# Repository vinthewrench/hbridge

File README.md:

# Actuator Controller – I²C Smart H-Bridge Board

This board is a smart linear actuator controller that uses a VNH7100BAS H-bridge with current sensing and I²C control. It is designed for 12 V actuators, supports stall/jam detection, and is chainable over I²C so you can run multiple actuators from one controller without burning GPIO pins.

This board is part of my distributed control system and is compatible with my nodeLync I²C wiring standard.

## Features
- Drives 12 V linear actuators (extend/retract)
- Solid-state H-bridge (no relays to weld shut)
- Current sensing for stall/jam detection
- I²C control using MCP23008 GPIO expander
- Optional MCP3427 ADC for current telemetry
- Motor power terminal or Anderson Powerpole input
- Status LEDs for power and activity
- Designed for Raspberry Pi or microcontroller systems
- Open hardware – modify it, build it, use it

## I²C Addresses
	| Device        | Base Address | Configurable         |
	|---------------|--------------|----------------------|
	| MCP23008 GPIO | 0x20–0x27    | Yes (A0–A2 jumpers)  |
	| MCP3427 ADC   | 0x68–0x6B    | Yes (ADDR pin)       |

## Current Measurement
The VNH7100BAS provides a current sense output. In 12-bit mode:
Useful for overload protection and detecting mechanical faults.

## Documentation
Full design writeup:
https://www.vinthewrench.com/p/the-humble-actuator

Demo video:
https://youtu.be/HOyxq8rQfaQ

## Status
✅ Prototype tested  
✅ Verified on Raspberry Pi  
✅ Load tested with Progressive Automations PA-10 and PA-14 actuators  
✅ Ready for fabrication / community mods

## License
This is Open Hardware under the CERN-OHL-P v2 license.

You can build it, modify it, use it commercially, and keep modifications private if you want. Just do not remove the original credit.

SPDX-License-Identifier: CERN-OHL-P-2.0  
© 2025 Vinnie Moscaritolo

## Contributions
Issues and pull requests are welcome. If you build one, I would like to see it.

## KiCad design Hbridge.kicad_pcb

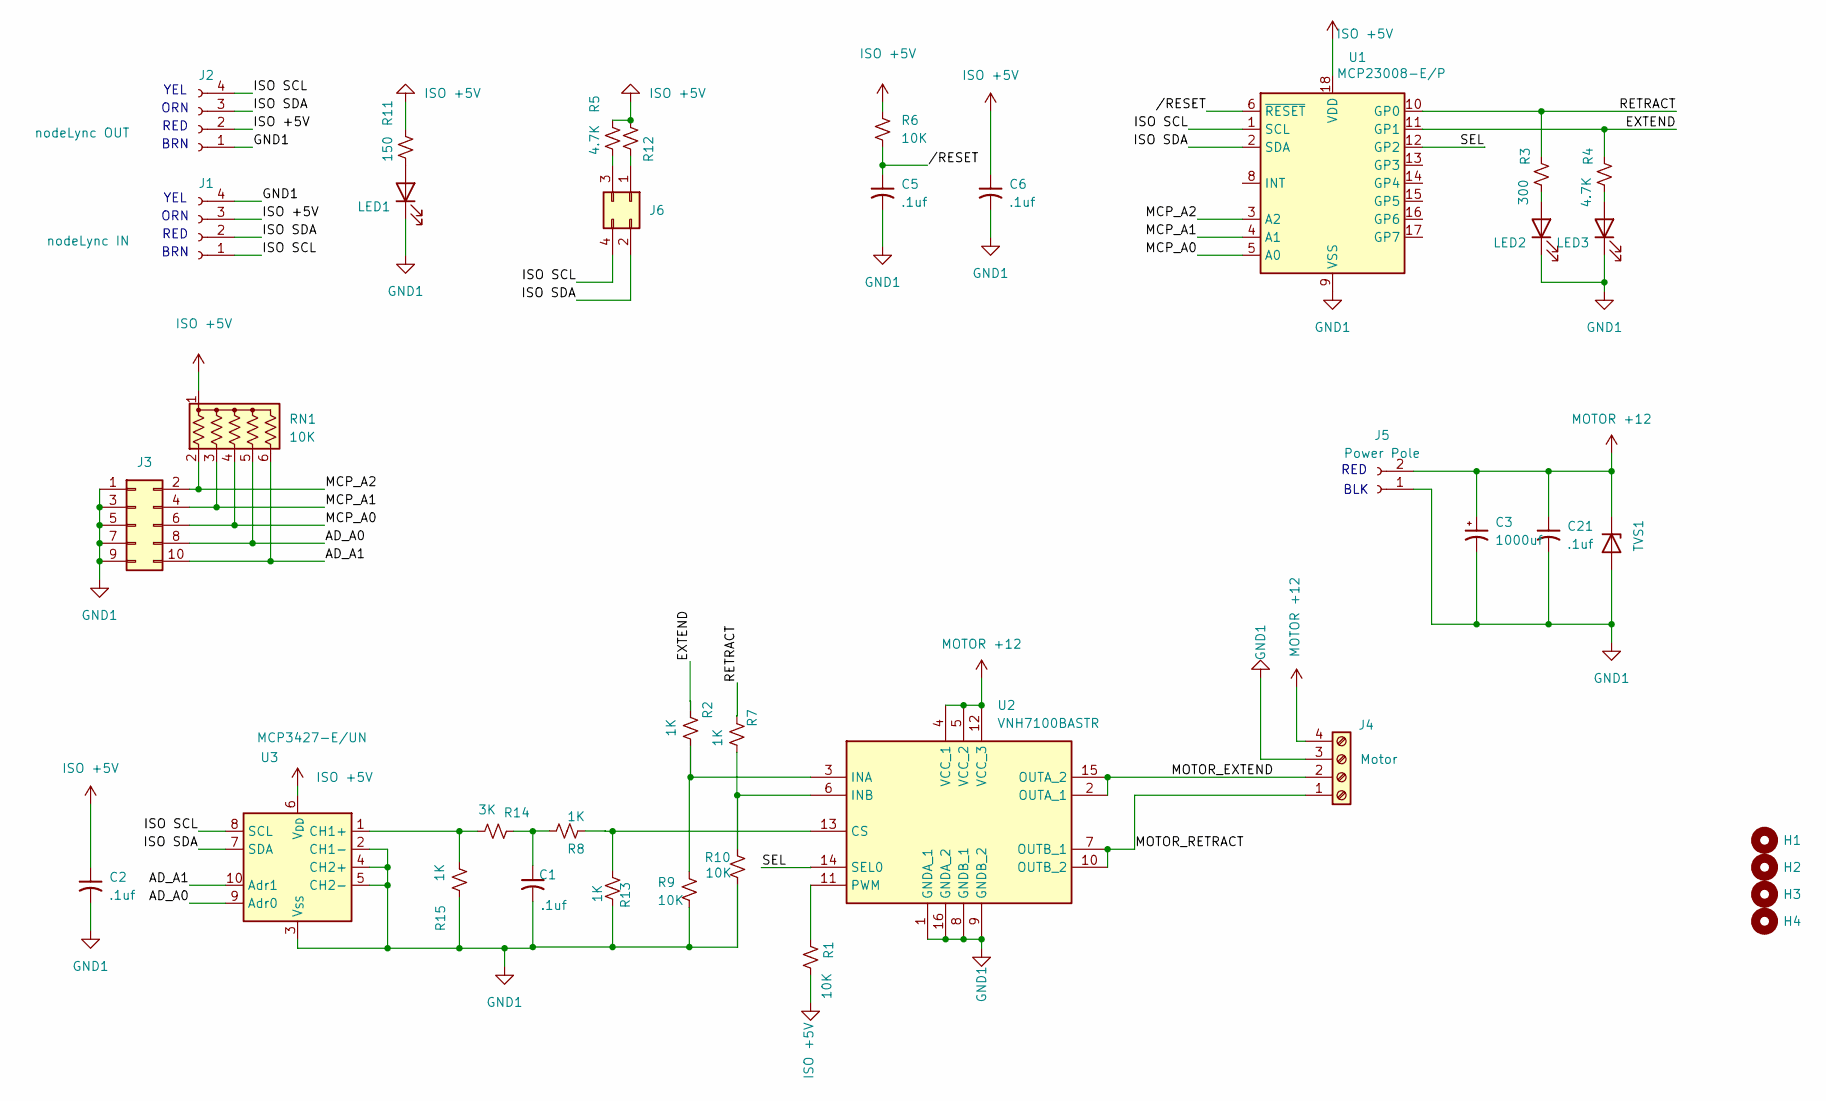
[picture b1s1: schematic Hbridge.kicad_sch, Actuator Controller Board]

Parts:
C1, C2, C5, C6, C21: .1uf; RCER71H104K0DBH03A
C3: 1000uf; CP_Radial_D10.0mm_P5.00mm
H1, H2, H3, H4: MountingHole
J1: nodeLync IN; PinHeader_1x04_P2.54mm_Horizontal
J2: nodeLync OUT; PinHeader_1x04_P2.54mm_Horizontal
J3: Conn_02x05_Odd_Even; PinHeader_2x05_P2.54mm_Vertical
J4: Motor; TerminalBlock_Phoenix_MKDS-1,5-4-5.08_1x04_P5.08mm_Horizont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
J5: Power Pole; 45A-VERT-PAIR
J6: Conn_02x02_Odd_Even; PinHeader_2x02_P2.54mm_Vertical
LED1, LED2, LED3: 151033GS03000; LED_D3.0mm
R1, R6, R9, R10: 10K; R_Axial_DIN0204_L3.6mm_D1.6mm_P7.62mm_Horizontal
R2, R7, R8, R13, R15: 1K; R_Axial_DIN0204_L3.6mm_D1.6mm_P7.62mm_Horizontal
R3: 300; R_Axial_DIN0204_L3.6mm_D1.6mm_P7.62mm_Horizontal
R4, R5, R12: 4.7K; R_Axial_DIN0204_L3.6mm_D1.6mm_P7.62mm_Horizontal
R11: 150; R_Axial_DIN0204_L3.6mm_D1.6mm_P7.62mm_Horizontal
R14: 3K; R_Axial_DIN0204_L3.6mm_D1.6mm_P7.62mm_Horizontal
RN1: 10K; R_Array_SIP6
TVS1: P6SMB18A; D_SMB_Handsoldering
U1: MCP23008-E/P; DIP-18_W7.62mm
U2: VNH7100BASTR; SOIC127P600X175-16N; Manufacturer_Part_Number VNH7100BASTR; Mouser Part Number 511-VNH7100BASTR
U3: MCP3427-E/UN; MSOP-10_3x3mm_P0.5mm

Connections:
/AD_A0: J3.8, RN1.5 (R4), U3.9 (Adr0)
/AD_A1: J3.10, RN1.6 (R5), U3.10 (Adr1)
/EXTEND: R2.2, R4.2, U1.11 (GP1)
/ISO SCL: J1.1, J2.4, J6.4, U1.1 (SCL), U3.8 (SCL)
/ISO SDA: J1.2, J2.3, J6.2, U1.2 (SDA), U3.7 (SDA)
/MCP_A0: J3.6, RN1.4 (R3), U1.5 (A0)
/MCP_A1: J3.4, RN1.3 (R2), U1.4 (A1)
/MCP_A2: J3.2, RN1.2 (R1), U1.3 (A2)
/MOTOR_EXTEND: J4.2, U2.2 (OUTA_1), U2.15 (OUTA_2)
/MOTOR_RETRACT: J4.1, U2.7 (OUTB_1), U2.10 (OUTB_2)
/RETRACT: R3.2, R7.2, U1.10 (GP0)
/SEL: U1.12 (GP2), U2.14 (SEL0)
//RESET: C5.1, R6.2, U1.6 (~RESET)
GND1: C1.2, C2.2, C3.2, C5.2, C6.2, C21.2, J1.4, J2.1, J3.1, J3.3, J3.5, J3.7, J3.9, J4.3, J5.1, LED1.1 (K), LED2.1 (K), LED3.1 (K), R9.2, R10.2, R13.1, R15.2, TVS1.2 (A), U1.9 (VSS), U2.1 (GNDA_1), U2.8 (GNDB_1), U2.9 (GNDB_2), U2.16 (GNDA_2), U3.2 (CH1-), U3.3 (V_{SS}), U3.4 (CH2+), U3.5 (CH2-)
ISO +5V: C2.1, C6.1, J1.3, J2.2, R1.2, R5.2, R6.1, R11.2, R12.2, RN1.1 (common), U1.18 (VDD), U3.6 (V_{DD})
MOTOR +12: C3.1, C21.1, J4.4, J5.2, TVS1.1 (K), U2.4 (VCC_1), U2.5 (VCC_2), U2.12 (VCC_3)
unnamed: C1.1, R8.1, R14.2
unnamed: J6.1, R12.1
unnamed: J6.3, R5.1
unnamed: LED1.2 (A), R11.1
unnamed: LED2.2 (A), R3.1
unnamed: LED3.2 (A), R4.1
unnamed: R8.2, R13.2, U2.13 (CS)
unnamed: R2.1, R9.1, U2.3 (INA)
unnamed: R7.1, R10.1, U2.6 (INB)
unnamed: R1.1, U2.11 (PWM)
unnamed: R14.1, R15.1, U3.1 (CH1+)

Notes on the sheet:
ORN
YEL
BRN
RED
BLK
RED

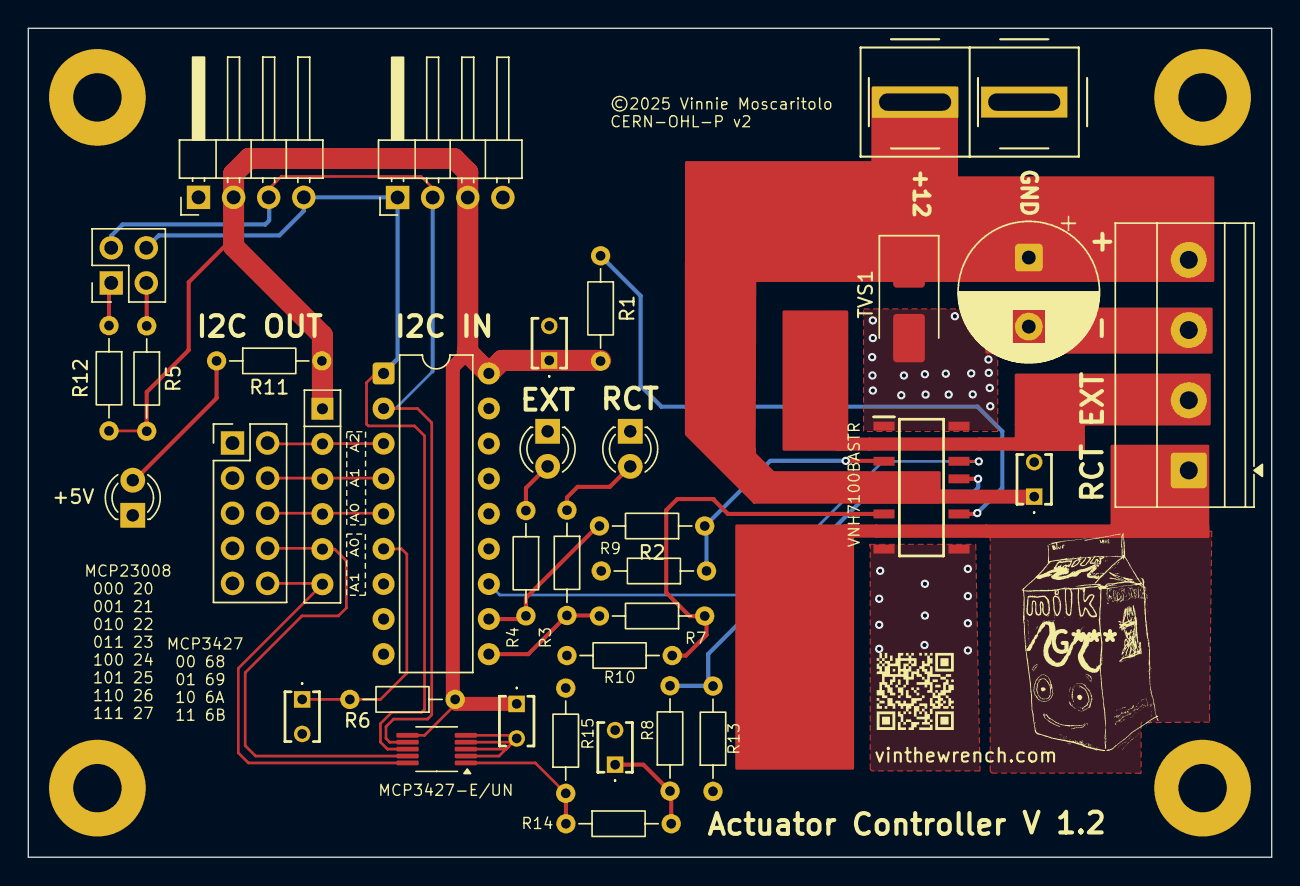
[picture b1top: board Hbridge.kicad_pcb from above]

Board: 2 copper layers, 90.0 x 60.0 mm, 39 parts (0 on the bottom side), 27 nets.

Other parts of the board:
H1#2, H1#3, H1#4: MountingHole_3.5mm_Pad

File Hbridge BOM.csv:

H-Bridge Bill of materials,,,,,,,
Quantity,Designator,Designation,Mfg Part,Supplier Part,Cost,Ext,Footprint
5,"C21,C5,C6,C2,C1",.1uf,RCER71H104K0DBH03A,81-RCER71H104K0DBH3A,$0.18 ,$0.92 ,Multilayer Ceramic Capacitors MLCC - Leaded .1UF 50V 10% 2.5MM
1,C3,1000uf,EEU-FR1E102,667-EEU-FR1E102,$0.45 ,$0.45 ,Aluminum Electrolytic Capacitors - Radial Leaded 25VDC 1000uF 10x20mm
2,"J1, J2",nodeLync socket,538-70551-0003,70551-0003,$1.19 ,$2.38 ,Molex Headers & Wire Housings SL 4 CKT W-T-B SHROU
,J3,Conn_02x05_Odd_Even,,,,0,
1,J4,Screw_Terminal_01x4,1715747,651-1715747,$2.21 ,$2.21 ,Fixed Terminal Blocks 4P 5.08mm 90DEG
1,J5,45A-VERT-PAIR,SSQ-108-04-L-D,200-SSQ10804LD,$3.28 ,$3.28 ,Heavy Duty Power Connectors PP PCB STRAIGHT
1,J6,Conn_02x02_Odd_Even,,,,0,
3,"LED3,LED2,LED1",LED 3mm Green/Red,151033GS03000,710-151033GS03000,$0.25 ,$0.75 ,Single Color LEDs WL-TMRW THT Mono Waterclr Rnd 3mm Grn
4,"R4,R12,R5,R3",4.7K,MBA02040C4701FRP00,594-5063JD4K700FT,$0.11 ,$0.44 ,Metal Film Resistors - Through Hole .4watt 4.7Kohms 1% 1/8watt
1,R11,150,MBA02040C1500FRP00,594-5063JD150R0FT,$0.10 ,$0.10 ,Metal Film Resistors - Through Hole .4watt 150ohms 1% 1/8watt
6,"R6,R14,R15,R9,R10,R1",10K,MBA02040C1002FRP00,594-5063JD10K1%TR,$0.10 ,$0.60 ,Metal Film Resistors - Through Hole .4watt 10Kohms 1% 1/8watt
3,"R7,R8,R2",1K,MBA02040C1001FRP00,594-5063JD1K000FT,$0.10 ,$0.30 ,Metal Film Resistors - Through Hole .4watt 1Kohms 1% 1/8watt
1,RN1,10K,4606M-101-103LF,652-4606M-1LF-10K,0.57,0.57,Resistor Networks & Arrays 6pins 10Kohms Bussed
8,TSV1,P6SMB18A,P6SMB18A,652-P6SMB18A,$0.22 ,$1.76 ,ESD Protection Diodes / TVS Diodes 18V 600W UniDir
1,U1,MCP23008-E/P,MCP23008-E/P,579-MCP23008-E/P,$1.54 ,$1.54 ,Interface - I/O Expanders In/Out I2C int DIP
1,U2,VNH7100BASTR,VNH7100BASTR,511-VNH7100BASTR,$3.38 ,$3.38 ,Motor / Motion / Ignition Controllers & Drivers Low Side Driver 1.5A /3A A 595-DRV103H/2K5
1,U3,MCP3427-E/UN,,579-MCP3427E/UN,$3.68 ,$3.68 ,
1,PCB,PCBoard 60*90,,,$0.65 ,$0.65 ,PCBway board 
,,,,,,,
,,,,,Total Cost,$23.01 ,

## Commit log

2025-10-11 no message
2025-10-13 update BOM
2025-10-18 corrected issues with sense resistor for CS and SEL

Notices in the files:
Hbridge.kicad_sch:
CERN-OHL-P v2 Permissive Open Hardware Licence
